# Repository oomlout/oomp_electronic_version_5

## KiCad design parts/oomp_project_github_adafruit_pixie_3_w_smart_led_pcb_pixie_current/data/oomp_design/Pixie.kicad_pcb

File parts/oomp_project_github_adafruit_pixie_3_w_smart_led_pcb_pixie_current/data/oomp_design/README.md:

# OOMP KiCad design copy

Open `Pixie.kicad_pro` (or the `.kicad_pcb` / `.kicad_sch`) in KiCad. Local OOMP libraries are under `libraries/`. Original inputs are preserved in [../original/](../original/).

Only verified unchanged installed KiCad defaults were renamed. Modified, custom, unmatched and unavailable items remain unchanged. Soldering variants are never swapped during conversion. Existing pad coordinates, nets and UUIDs are preserved.

See [conversion_report.yaml](conversion_report.yaml) for every conversion and skip. Copy this directory before editing; regeneration refuses to overwrite edited design files.

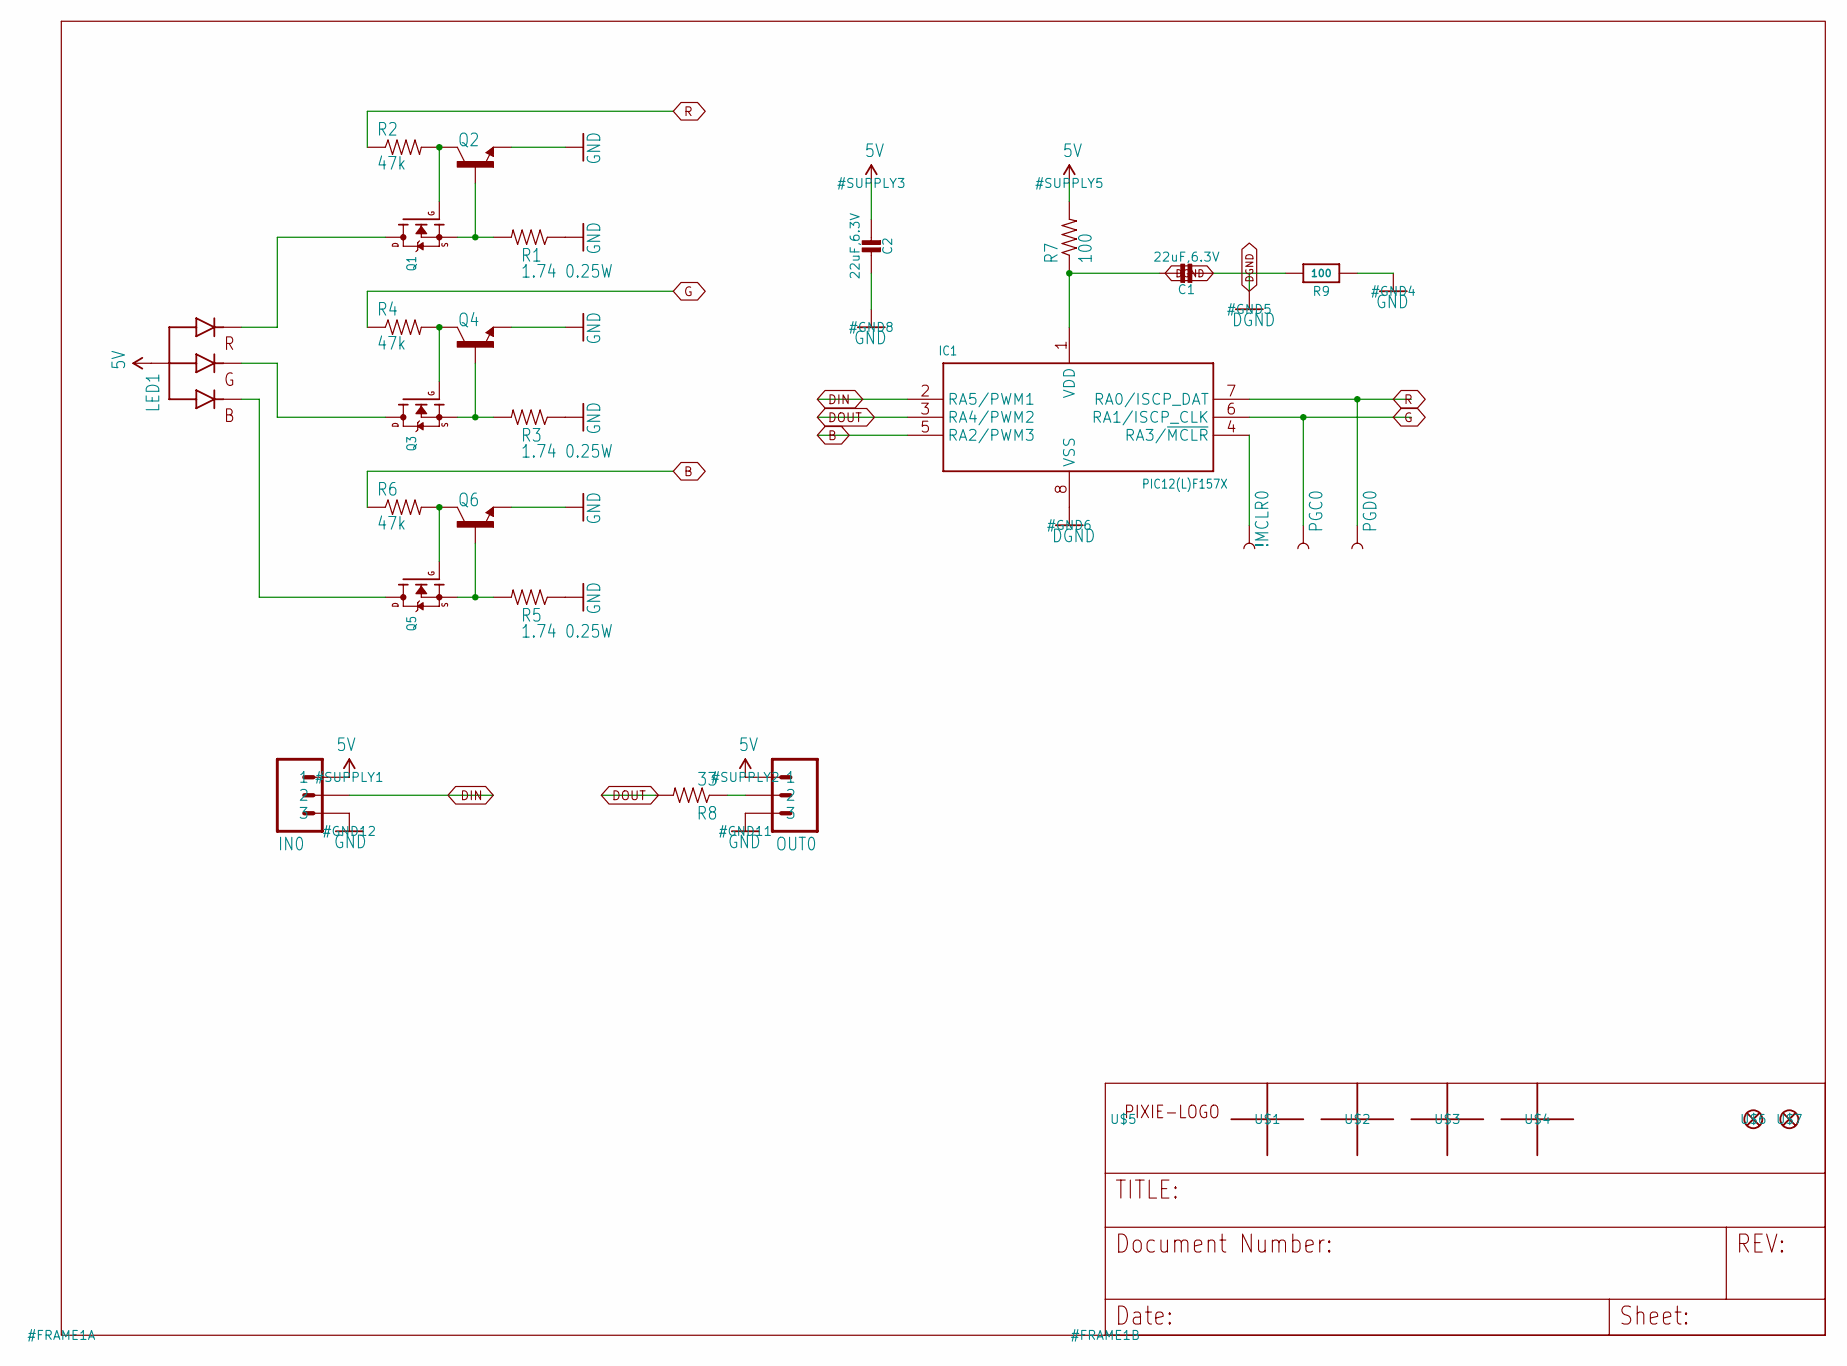
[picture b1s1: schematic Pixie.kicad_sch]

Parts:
!MCLR0: TEST-POINT3X4; PAD.03X.04
C1, C2: 22uF,6.3V; _0805MP
IC1: PIC12(L)F157X; MSOP-8
IN0: M030.1PWR+SIG; 1X03-0.1PWR+SIG
LED1: RGBLED_CA; RGBLED3W4PIN
OUT0: M030.1PWR+SIG; 1X03-0.1PWR+SIG
PGC0: TEST-POINT3X4; PAD.03X.04
PGD0: TEST-POINT3X4; PAD.03X.04
Q1, Q3, Q5: IRLML2060TRPBF; SOT23-3
Q2, Q4, Q6: MMBT2222A; SOT23-3
R1, R3, R5: 1.74 0.25W; 1206
R2, R4, R6: 47k; 0603-RES
R7: 100; 0603-RES
R8: 33; 0603-RES
R9: 100; _0603MP
U$1, U$2, U$3, U$4: ALIGN_CROSS
U$5: PIXIE-LOGO
U$6, U$7: FIDUCIAL""; FIDUCIAL_1MM

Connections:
5V: C2.2, IN0.P$1 (1), LED1.ANODE (VCC), OUT0.P$1 (1), R7.2
B: IC1.5 (RA2/PWM3), R6.1
DGND: C1.2, IC1.8 (VSS), R9.2
DIN: IC1.2 (RA5/PWM1), IN0.P$2 (2)
DOUT: IC1.3 (RA4/PWM2), R8.2
G: IC1.6 (RA1/ISCP_CLK), PGC0.P$1, R4.1
GND: C2.1, IN0.P$3 (3), OUT0.P$3 (3), Q2.2 (E), Q4.2 (E), Q6.2 (E), R1.1, R3.1, R5.1, R9.1
unnamed: LED1.R (RED), Q1.3 (D)
unnamed: LED1.G (GREEN), Q3.3 (D)
unnamed: LED1.B (BLUE), Q5.3 (D)
unnamed: Q1.2 (S), Q2.1 (B), R1.2
unnamed: Q3.2 (S), Q4.1 (B), R3.2
unnamed: OUT0.P$2 (2), R8.1
unnamed: !MCLR0.P$1, IC1.4 (RA3/~MCLR)
unnamed: Q5.1 (G), Q6.3 (C), R6.2
unnamed: Q3.1 (G), Q4.3 (C), R4.2
unnamed: C1.1, IC1.1 (VDD), R7.1
unnamed: Q5.2 (S), Q6.1 (B), R5.2
unnamed: Q1.1 (G), Q2.3 (C), R2.2
R: IC1.7 (RA0/ISCP_DAT), PGD0.P$1, R2.1

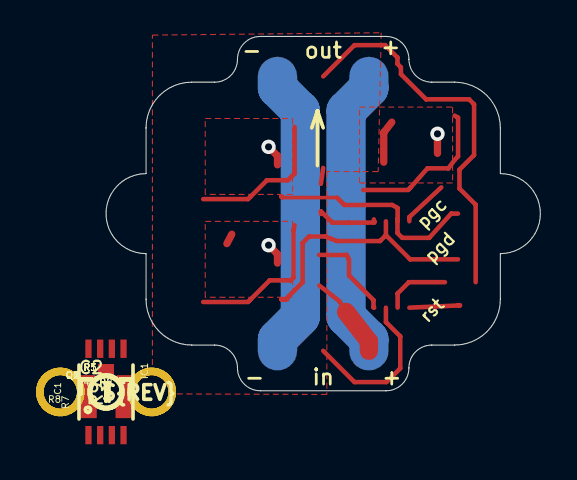
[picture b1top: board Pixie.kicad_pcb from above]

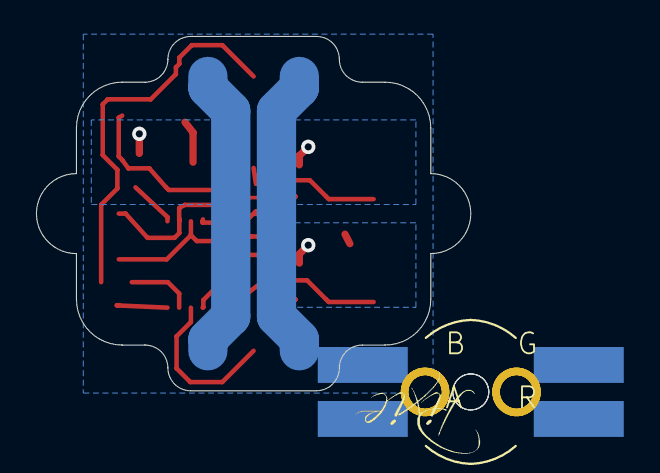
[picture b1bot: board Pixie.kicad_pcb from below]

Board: 16 copper layers, 24.1 x 19.7 mm, 34 parts (2 on the bottom side), 20 nets.

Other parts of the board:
U$8: PCBFEAT-REV-040
UNK_HOLE_0: dummyfp0
UNK_HOLE_1: dummyfp1

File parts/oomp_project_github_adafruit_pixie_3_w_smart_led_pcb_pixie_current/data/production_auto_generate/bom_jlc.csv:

Comment,Designator,Footprint,LCSC Part #
,U$8,Pixie-import-fps:PCBFEAT-REV-040,
1.74 0.25W,"R1,R3,R5",Pixie-import-fps:1206,
100,R7,Pixie-import-fps:0603-RES,C22775
100,R9,Pixie-import-fps:_0603MP,C22775
"22uF,6.3V","C1,C2",Pixie-import-fps:_0805MP,
33,R8,Pixie-import-fps:0603-RES,C23140
47k,"R2,R4,R6",Pixie-import-fps:0603-RES,C2907042
ALIGN_CROSS,"U$1,U$2,U$3,U$4",Pixie-import-fps:ALIGN_CROSS,
"FIDUCIAL""""","U$6,U$7",Pixie-import-fps:FIDUCIAL_1MM,
IRLML2060TRPBF,"Q1,Q3,Q5",Pixie-import-fps:SOT23-3,
MMBT2222A,"Q2,Q4,Q6",Pixie-import-fps:SOT23-3,
PIC12(L)F157X,IC1,Pixie-import-fps:MSOP-8,
PIXIE-LOGO,U$5,Pixie-import-fps:PIXIE-LOGO,
RGBLED_CA,LED1,Pixie-import-fps:RGBLED3W4PIN,
TEST-POINT3X4,"!MCLR0,PGC0,PGD0",Pixie-import-fps:PAD.03X.04,

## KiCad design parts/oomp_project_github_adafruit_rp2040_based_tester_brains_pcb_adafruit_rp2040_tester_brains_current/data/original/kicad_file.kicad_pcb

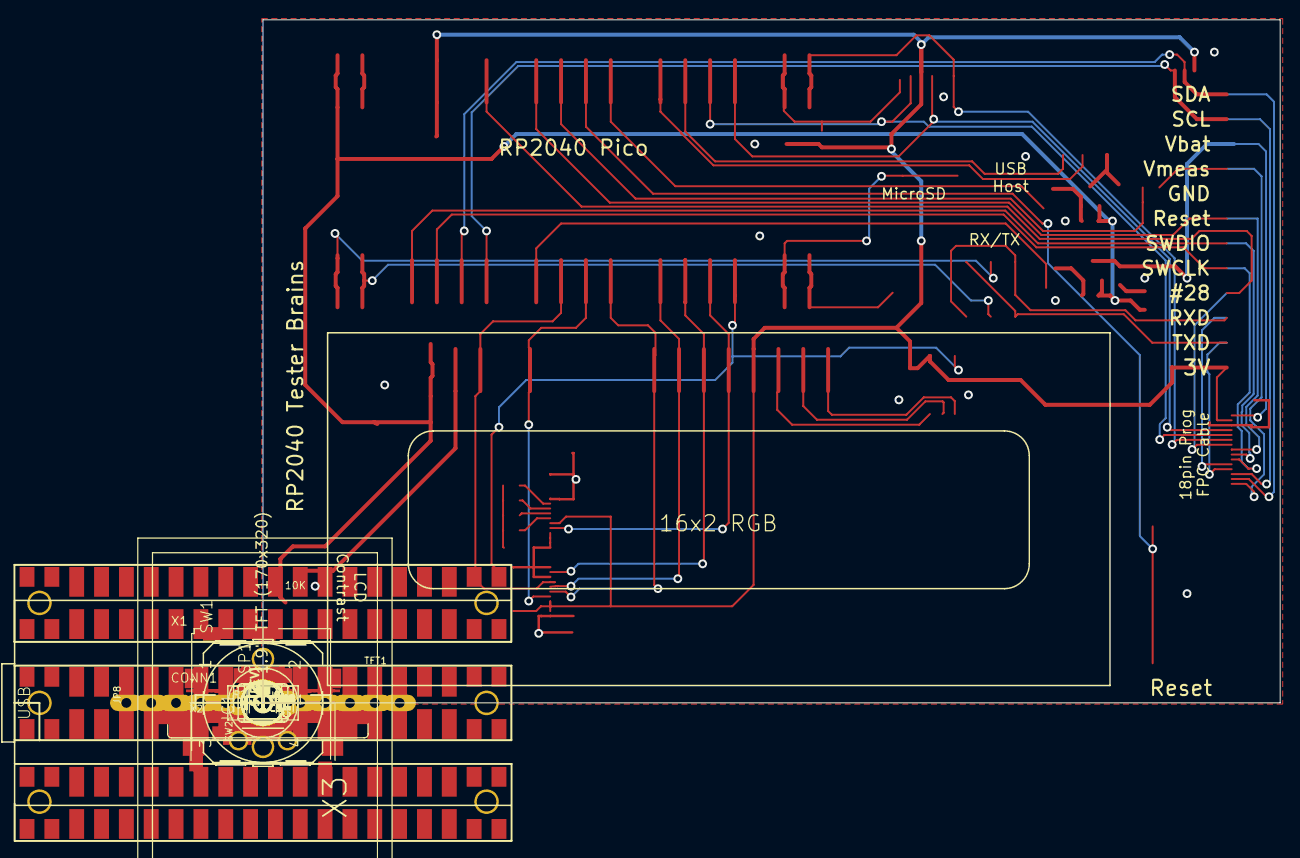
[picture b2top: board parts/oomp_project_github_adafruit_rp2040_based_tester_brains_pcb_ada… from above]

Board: 2 copper layers, 104.0 x 69.8 mm, 48 parts (0 on the bottom side), 47 nets.

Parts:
C1, C2, C3, C4, C5, C6, C7, C8, C9: 10uF; 0805-NO
CB1: PICOWBELL_DUALSMT
CONN1: STEMMA_I2C_QT; JST_SH4
FID1, FID2, FID3: FIDUCIAL_1MM
IC1: WS2811-SOP8; SO08-SKINNYPADS
JP1: 16x2 LCD; 2X20_SMT_MALE
JP8: 1X12_OVAL
Q1, Q2: DMG34x5; SOT23-WIDE
Q3, Q4, Q5: BSS138; SOT23-WIDE
R1, R2, R3, R4, R5: 10K; 0603-NO
R6, R7, R8, R9: 27; 0603-NO
SP1: SPEAKER/PS12; PS12
SW1: 12mm SMT; B3F-40XX-SMT
SW2: DPDT SLIDE; EG1390
TFT1: DISP_LCD_ST7789_1.9IN_SS; TFT_1.9IN_170X320_30P_SS
TP1, TP2, TP3, TP4: SEWTAP_SMTNUTM3; SMT_NUT_3MM
U$7, U$8, U$9, U$10: MOUNTINGHOLE3.0THIN; MOUNTINGHOLE_3.0_PLATEDTHIN
U$13: PCBFEAT-REV-040
VR1: 10K Trimmer; TRIMPOT_BOURNS_TC33X-2
X1: USB A; USB_HOST-SMT
X2: MicroSD; MICROSD
X3: TESTER_PROGCABLE_FLIP; FPC_0.5MM_18PIN

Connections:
3.3V: C2.1, C3.1, C5.1, C6.1, C7.1, CB1.S71, CB1.S72, CONN1.2, IC1.8, JP1.29, JP1.30, JP8.12, R5.1, TFT1.2, TFT1.3, TFT1.4, TFT1.20, X2.4, X3.2
+5V: C8.1, C9.1, CB1.S79, CB1.S80, JP1.3, JP1.4, Q1.2, Q2.2, R3.2, R4.2, VR1.1
GND: C1.2, C2.2, C3.2, C4.2, C5.2, C6.2, C7.2, C8.2, C9.2, CB1.S5, CB1.S6, CB1.S15, CB1.S16, CB1.S25, CB1.S26, CB1.S35, CB1.S36, CB1.S45, CB1.S46, CB1.S55, CB1.S56, CB1.S65, CB1.S66, CB1.S75, CB1.S76, CONN1.1, CONN1.MT1, CONN1.MT2, IC1.4, JP1.1, JP1.2, JP1.9, JP1.10, JP8.5, Q3.2, Q4.2, Q5.2, R2.1, SP1.P$1, SW1.P$3, SW1.P$4, TFT1.1, TFT1.9, TFT1.11, TFT1.12, TFT1.13, TFT1.14, TFT1.15, TFT1.16, TFT1.17, TFT1.18, TFT1.25, TFT1.30, TFT1.MNT1, TFT1.MNT2, TP1.P$1, TP2.P$1, TP3.P$1, TP4.P$1, VR1.3, X1.GND, X2.6, X2.MT1, X2.MT2, X3.3, X3.SUPPORT1, X3.SUPPORT2
GPIO28: CB1.S67, CB1.S68, JP8.9, X3.7
LCD_BLUE: IC1.3, JP1.35, JP1.36
LCD_D4: CB1.S23, CB1.S24, JP1.21, JP1.22, TFT1.6
LCD_D5: CB1.S27, CB1.S28, JP1.23, JP1.24, TFT1.7
LCD_D6: CB1.S29, CB1.S30, JP1.25, JP1.26, TFT1.10
LCD_D7: CB1.S31, CB1.S32, JP1.27, JP1.28, TFT1.19
LCD_E: CB1.S21, CB1.S22, JP1.11, JP1.12, TFT1.5
LCD_GREEN: IC1.2, JP1.33, JP1.34
LCD_NEO: CB1.S33, CB1.S34, IC1.6, Q5.1
LCD_RED: IC1.1, JP1.31, JP1.32
LCD_RS: CB1.S19, CB1.S20, JP1.7, JP1.8, TFT1.8
LEDK: Q5.3, R6.1, R7.1, R8.1, R9.1
MISO: CB1.S41, CB1.S42, X2.7, X3.6
MOSI: CB1.S49, CB1.S50, X2.3, X3.5
unnamed: CB1.S39, CB1.S40, SP1.P$2
unnamed: R6.2, TFT1.21
unnamed: R7.2, TFT1.22
unnamed: R8.2, TFT1.23
unnamed: R9.2, TFT1.24
unnamed: JP1.5, JP1.6, VR1.2
RESET: CB1.S59, CB1.S60, SW1.P$1, SW1.P$2
RXD: CB1.S3, CB1.S4, SW2.P1
RXI: JP8.10, SW2.O2, SW2.S1, X3.11
SCK: CB1.S47, CB1.S48, X2.5, X3.4
SCL: CB1.S13, CB1.S14, CONN1.4, JP8.2, X3.13
SDA: CB1.S11, CB1.S12, CONN1.3, JP8.1, X3.14
SD_CD: CB1.S37, CB1.S38, X2.CD1, X2.CD2
SD_CS: CB1.S43, CB1.S44, R5.2, X2.2
SWCLK: CB1.S9, CB1.S10, JP8.8, X3.10
SWDIO: CB1.S7, CB1.S8, JP8.7, X3.9
TARGET_RESET: CB1.S63, CB1.S64, JP8.6, X3.8
TXD: CB1.S1, CB1.S2, SW2.P2
TXO: JP8.11, SW2.O1, SW2.S2, X3.12
USB_D+: CB1.S51, CB1.S52, X1.D+
USB_D-: CB1.S53, CB1.S54, X1.D-
VBAT: C1.1, JP8.3, Q2.3, X3.1
VBAT_SW: CB1.S17, CB1.S18, Q4.1
VMEAS: JP8.4, R1.2, X3.15
VMEAS_DIV2: CB1.S61, CB1.S62, R1.1, R2.2
VSYS: CB1.S77, CB1.S78
VUSB: C4.1, Q1.3, X1.VBUS
VUSB_SW: CB1.S57, CB1.S58, Q3.1
~VBAT_SW1: Q2.1, Q4.3, R4.1
~VBAT_SW2: Q1.1, Q3.3, R3.1

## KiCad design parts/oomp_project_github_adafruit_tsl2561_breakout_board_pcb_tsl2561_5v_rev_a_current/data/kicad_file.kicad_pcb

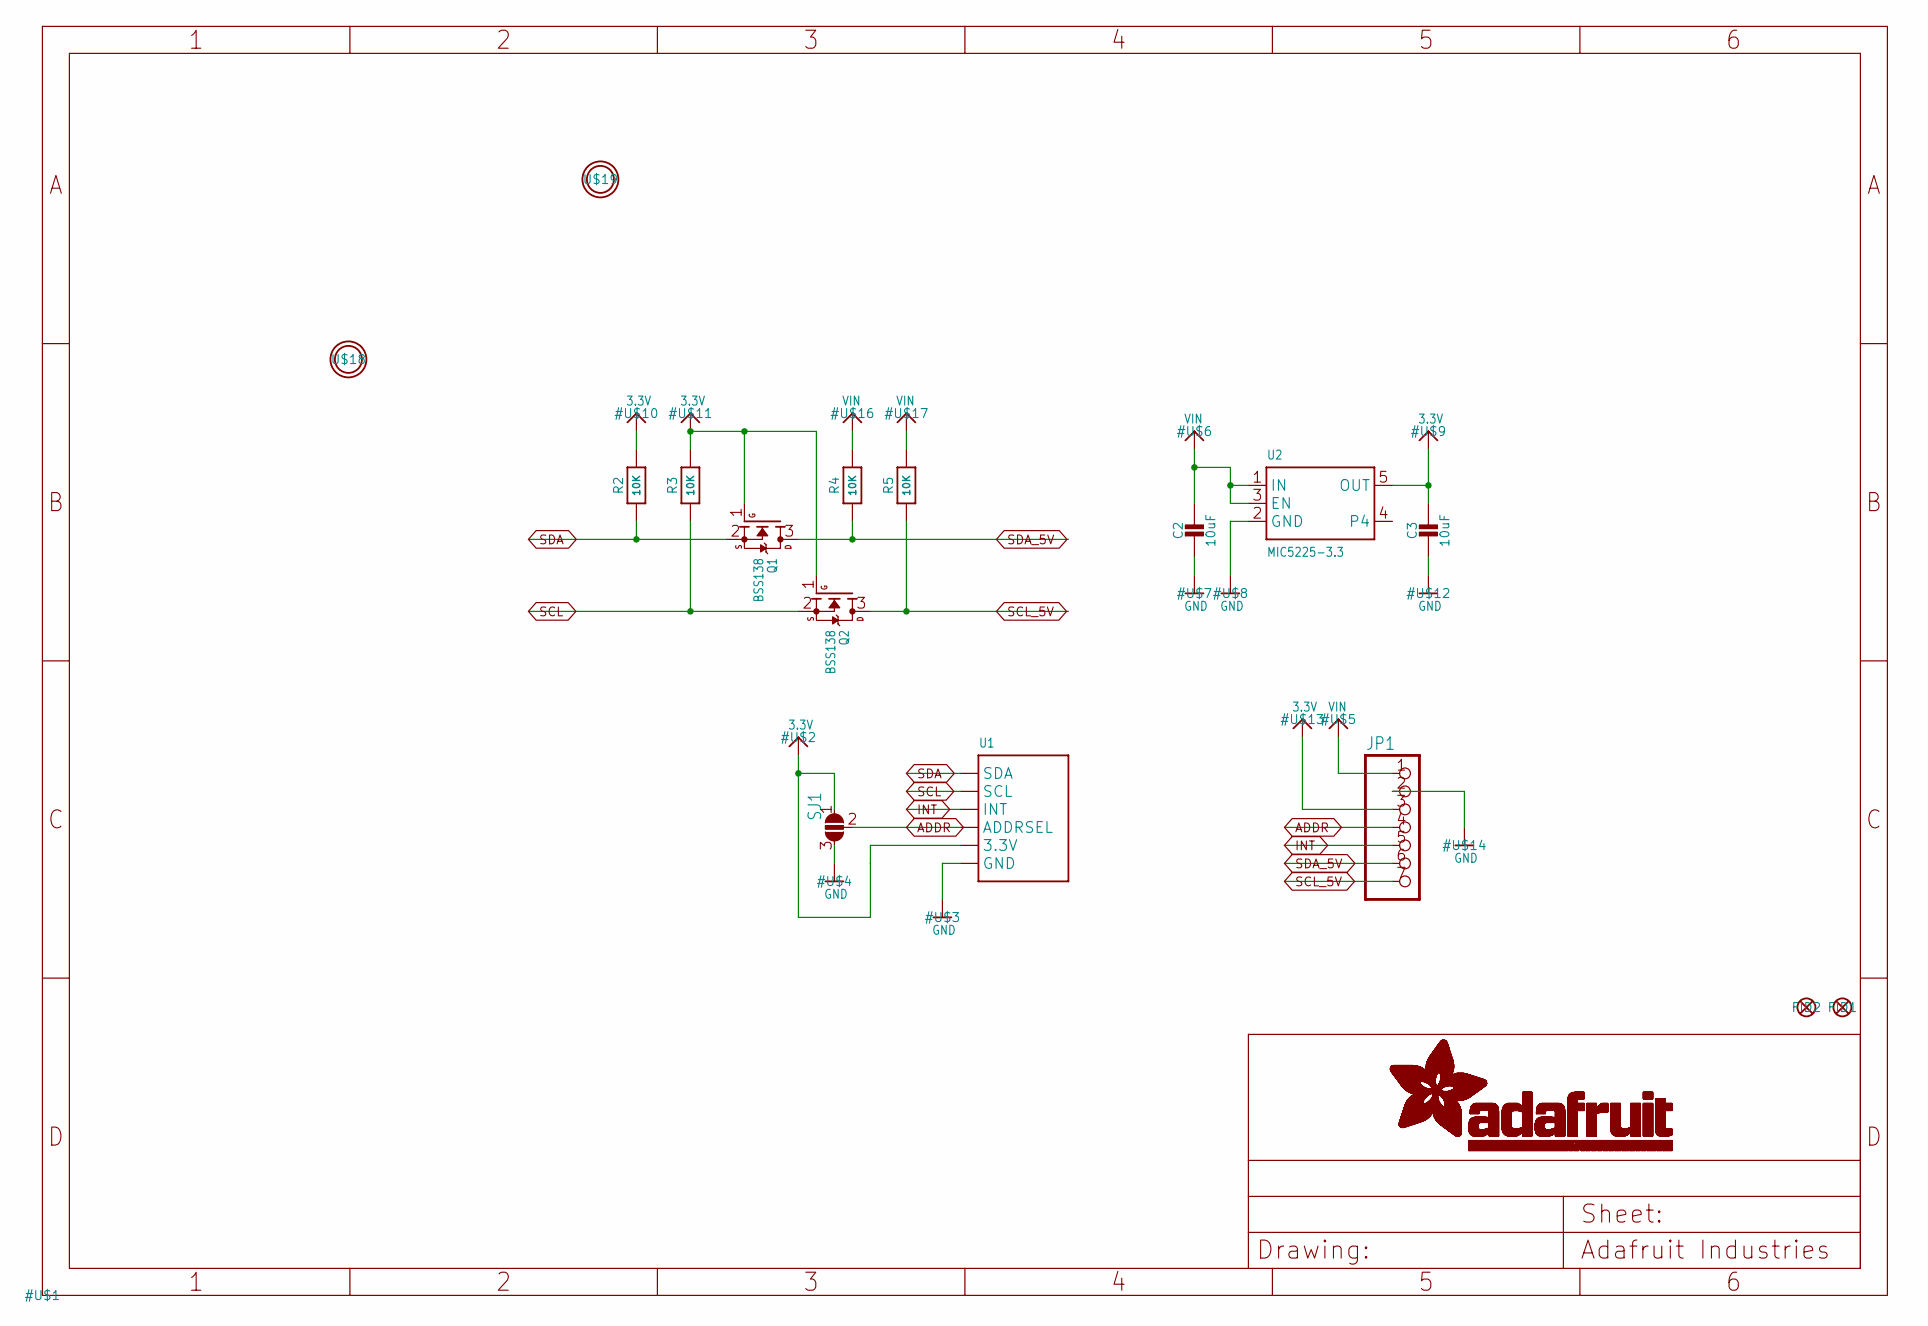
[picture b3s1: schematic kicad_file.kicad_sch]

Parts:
C2, C3: 10uF; 0805-NO
FID1, FID2: FIDUCIAL""; FIDUCIAL_1MM
JP1: HEADER-1X7THICKER; 1X07_ROUND_76
Q1, Q2: BSS138; SOT23-WIDE
R2, R3, R4, R5: 10K; 0805-NO
SJ1: SOLDERJUMPER_2WAY; SOLDERJUMPER_2WAY_OPEN_NOPASTE
U1: LIGHT_TSL2561; TSL2561_FN
U2: MIC5225-3.3; SOT23-5
U$18, U$19: MOUNTINGHOLE2.5; MOUNTINGHOLE_2.5_PLATED

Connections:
3.3V: C3.1, JP1.3, Q1.1 (G), Q2.1 (G), R2.2, R3.2, SJ1.1, U1.VDD (3.3V), U2.5 (OUT)
ADDR: JP1.4, SJ1.2, U1.ADR (ADDRSEL)
GND: C2.2, C3.2, JP1.2, SJ1.3, U1.VSS (GND), U2.2 (GND)
INT: JP1.5, U1.INT
SCL: Q2.2 (S), R3.1, U1.CLK (SCL)
SCL_5V: JP1.7, Q2.3 (D), R5.1
SDA: Q1.2 (S), R2.1, U1.DATA (SDA)
SDA_5V: JP1.6, Q1.3 (D), R4.1
VIN: C2.1, JP1.1, R4.2, R5.2, U2.1 (IN), U2.3 (EN)

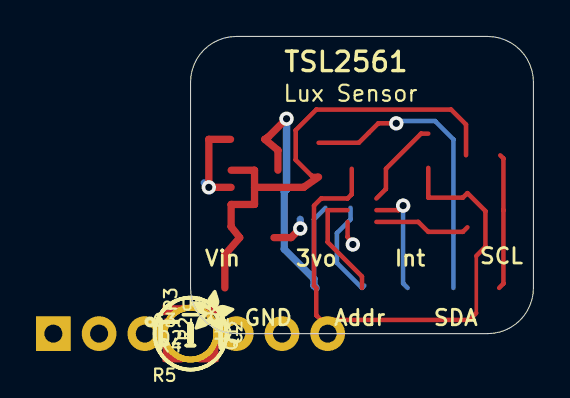
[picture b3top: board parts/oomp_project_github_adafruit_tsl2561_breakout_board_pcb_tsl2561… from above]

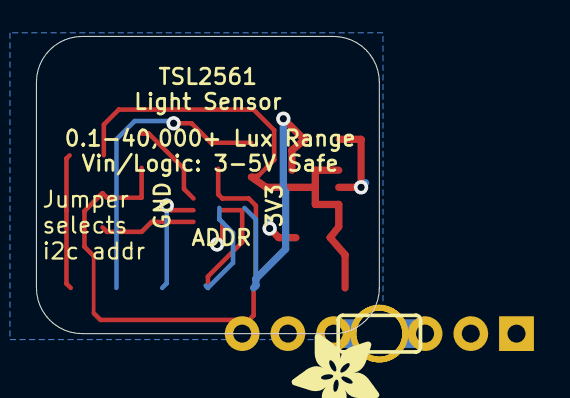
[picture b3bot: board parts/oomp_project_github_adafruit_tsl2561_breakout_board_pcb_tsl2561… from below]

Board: 2 copper layers, 19.1 x 16.5 mm, 18 parts (2 on the bottom side), 9 nets.

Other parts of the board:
U$15: ADAFRUIT_2.5MM
U$20: ADAFRUIT_5MM

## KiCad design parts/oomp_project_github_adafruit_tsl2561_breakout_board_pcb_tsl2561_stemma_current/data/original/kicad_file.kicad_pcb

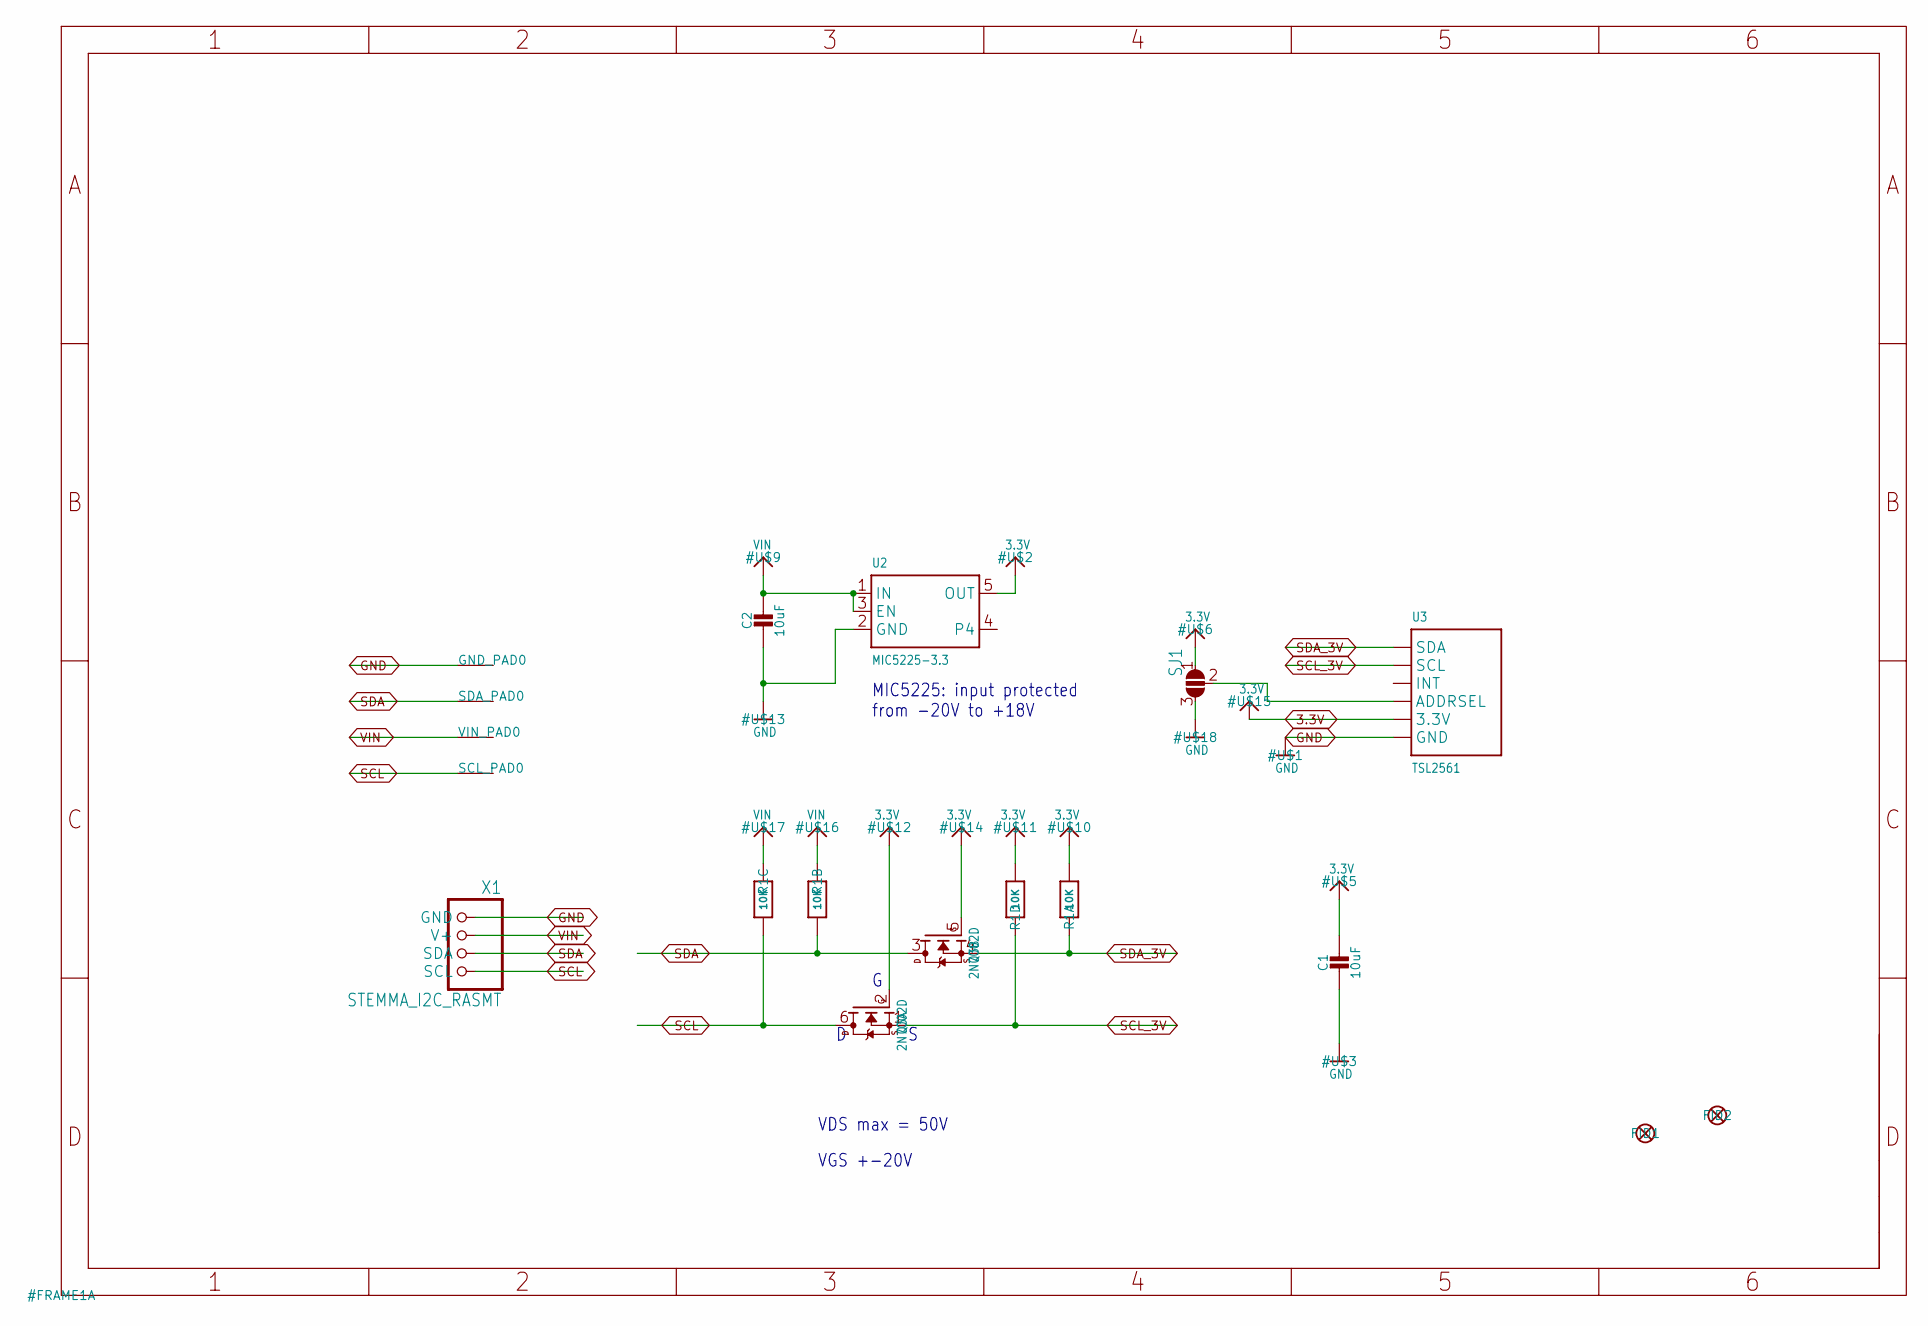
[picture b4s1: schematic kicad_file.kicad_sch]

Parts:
C1, C2: 10uF; 0805-NO
FID1, FID2: FIDUCIAL_1MM
GND_PAD0: SEWTAP-ALLIGATOR; SEWALLI
Q3: 2N7002D; SOT363
R1: 10K; RESPACK_4X0603
SCL_PAD0: SEWTAP-ALLIGATOR; SEWALLI
SDA_PAD0: SEWTAP-ALLIGATOR; SEWALLI
SJ1: SOLDERJUMPER_2WAY; SOLDERJUMPER_2WAY_OPEN_NOPASTE
U2: MIC5225-3.3; SOT23-5
U3: TSL2561; TSL2561_FN
VIN_PAD0: SEWTAP-ALLIGATOR; SEWALLI
X1: STEMMA_I2C_RASMT; JSTPH4

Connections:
3.3V: C1.1, Q3.2 (G), Q3.5 (G), R1.1, R1.5 (2), SJ1.1, U2.5 (OUT), U3.VDD (3.3V)
GND: C1.2, C2.2, GND_PAD0.P$1, SJ1.3, U2.2 (GND), U3.VSS (GND), X1.1 (GND)
unnamed: SJ1.2, U3.ADR (ADDRSEL)
SCL: Q3.6 (D), R1.6 (2), SCL_PAD0.P$1, X1.4 (SCL)
SCL_3V: Q3.1 (S), R1.4 (1), U3.CLK (SCL)
SDA: Q3.3 (D), R1.7 (2), SDA_PAD0.P$1, X1.3 (SDA)
SDA_3V: Q3.4 (S), R1.8 (2), U3.DATA (SDA)
VIN: C2.1, R1.2 (1), R1.3 (1), U2.1 (IN), U2.3 (EN), VIN_PAD0.P$1, X1.2 (V+)

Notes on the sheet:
VDS max = 50V
VGS +-20V
MIC5225: input protected from -20V to +18V

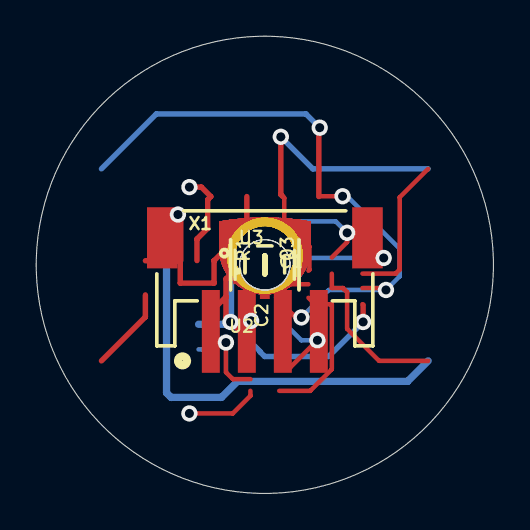
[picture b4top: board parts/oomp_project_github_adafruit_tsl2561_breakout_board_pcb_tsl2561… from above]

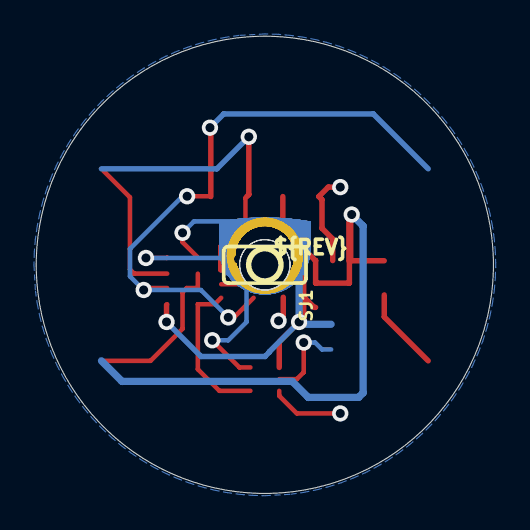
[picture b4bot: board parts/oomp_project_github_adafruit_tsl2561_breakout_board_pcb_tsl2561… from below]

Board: 2 copper layers, 25.4 x 25.4 mm, 19 parts (3 on the bottom side), 8 nets.

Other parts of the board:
U$4: STEMMA_TSL2561_B_FRONT
U$7: STEMMA_TSL2561_B_BACK
U$8: PCBFEAT-REV-040
UNK_HOLE_0: dummyfp0
UNK_HOLE_1: dummyfp1

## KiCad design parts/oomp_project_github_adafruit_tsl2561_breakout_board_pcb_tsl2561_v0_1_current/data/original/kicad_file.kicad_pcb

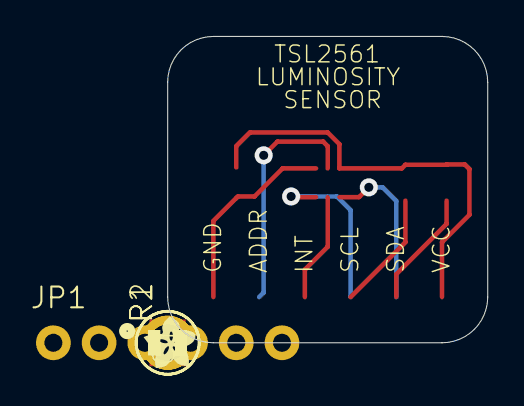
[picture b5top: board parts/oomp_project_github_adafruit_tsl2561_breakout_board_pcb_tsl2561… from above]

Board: 2 copper layers, 17.8 x 17.0 mm, 10 parts (0 on the bottom side), 6 nets.

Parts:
C1: 0.1uF; C0805
JP1: 1X06_ROUND_76
R1, R2: 10K; R0805
U1: TSL2561; TSL2561_FN
U$2, U$4: FIDUCIAL; FIDUCIAL_1MM
U$5, U$6: MOUNTINGHOLE2.0; MOUNTINGHOLE_2.0_PLATED
U$7: ADAFRUIT200MIL

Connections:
ADDR: JP1.2, U1.ADR
GND: C1.2, JP1.1, U1.VSS
INT: JP1.3, U1.INT
SCL: JP1.4, R2.1, U1.CLK
SDA: JP1.5, R1.1, U1.DATA
VCC: C1.1, JP1.6, R1.2, R2.2, U1.VDD

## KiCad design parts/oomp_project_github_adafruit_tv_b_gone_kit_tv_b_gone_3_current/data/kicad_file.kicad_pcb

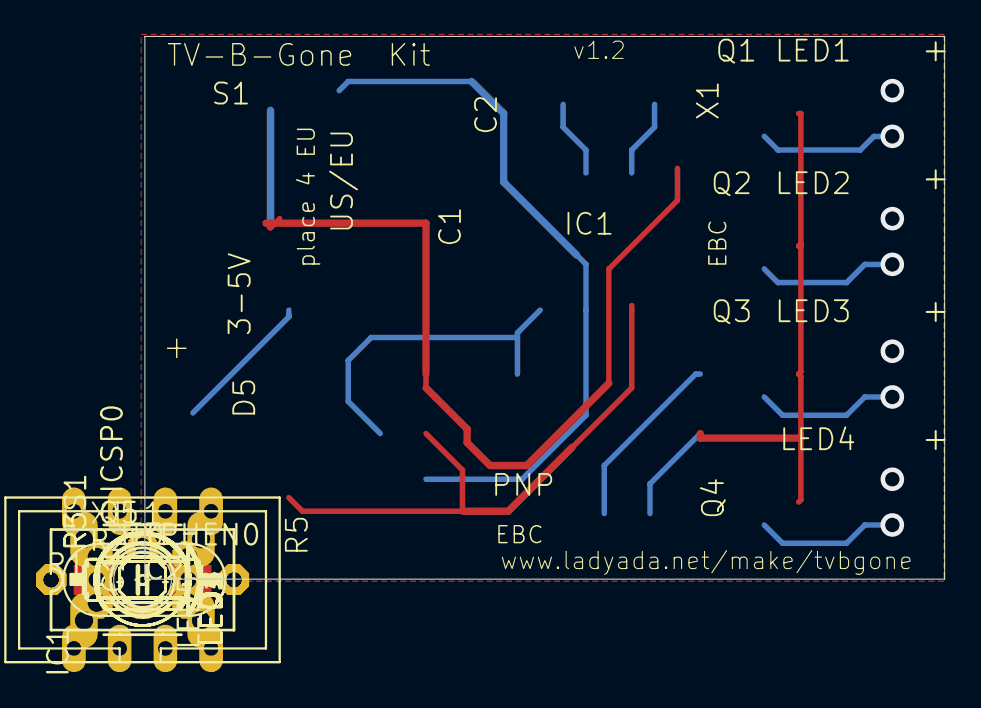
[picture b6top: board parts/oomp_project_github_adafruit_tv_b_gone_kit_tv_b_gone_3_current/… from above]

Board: 16 copper layers, 44.4 x 30.1 mm, 23 parts (0 on the bottom side), 15 nets.

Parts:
+0: 1X01
C1: 0.1uF; C025-025X050
C2: 100uF; E2,5-5
HYPHEN0: 1X01
IC1: ATTINY85V-10P; DIL08
ICSP0: PINHD-2X3THM; ISP6
LED1, LED2, LED3, LED4: LED; 5MM-SIDE
LED5: RED; LED3MM
Q1, Q2, Q3, Q4: 2N3904; TO92-EZ
Q5: MPS2907A; TO92-CBE
R1: 1.0 K; 0207_10
R2: 10K (opt); 0207_10
R3: 10K; 0207_10
R5: 1K; 0207_10
S1: B3F-10XX
UNK_HOLE_0: dummyfp0
XTL1: 8.0MHz; CERM_OSC

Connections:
GND: C1.2, C2.-, HYPHEN0.1, IC1.4, ICSP0.6, Q1.3, Q2.3, Q3.3, Q4.3, R2.1, R3.1, S1.1, S1.2, XTL1.P$2
MISO: IC1.6, ICSP0.1, R3.2
MOSI: IC1.5, ICSP0.4, R1.2
unnamed: IC1.3, XTL1.P$1
unnamed: IC1.2, XTL1.P$3
unnamed: LED5.K, R5.2
unnamed: Q5.B, R1.1
unnamed: LED4.K, LED4.K2, Q4.1
unnamed: LED2.K, LED2.K2, Q2.1
unnamed: LED3.K, LED3.K2, Q3.1
unnamed: Q1.2, Q2.2, Q3.2, Q4.2, Q5.C, R2.2
unnamed: LED1.K, LED1.K2, Q1.1
RST: IC1.1, ICSP0.5, S1.3, S1.4
SCK: IC1.7, ICSP0.3, R5.1
VCC: +0.1, C1.1, C2.+, IC1.8, ICSP0.2, LED1.A, LED1.A2, LED2.A, LED2.A2, LED3.A, LED3.A2, LED4.A, LED4.A2, LED5.A, Q5.E

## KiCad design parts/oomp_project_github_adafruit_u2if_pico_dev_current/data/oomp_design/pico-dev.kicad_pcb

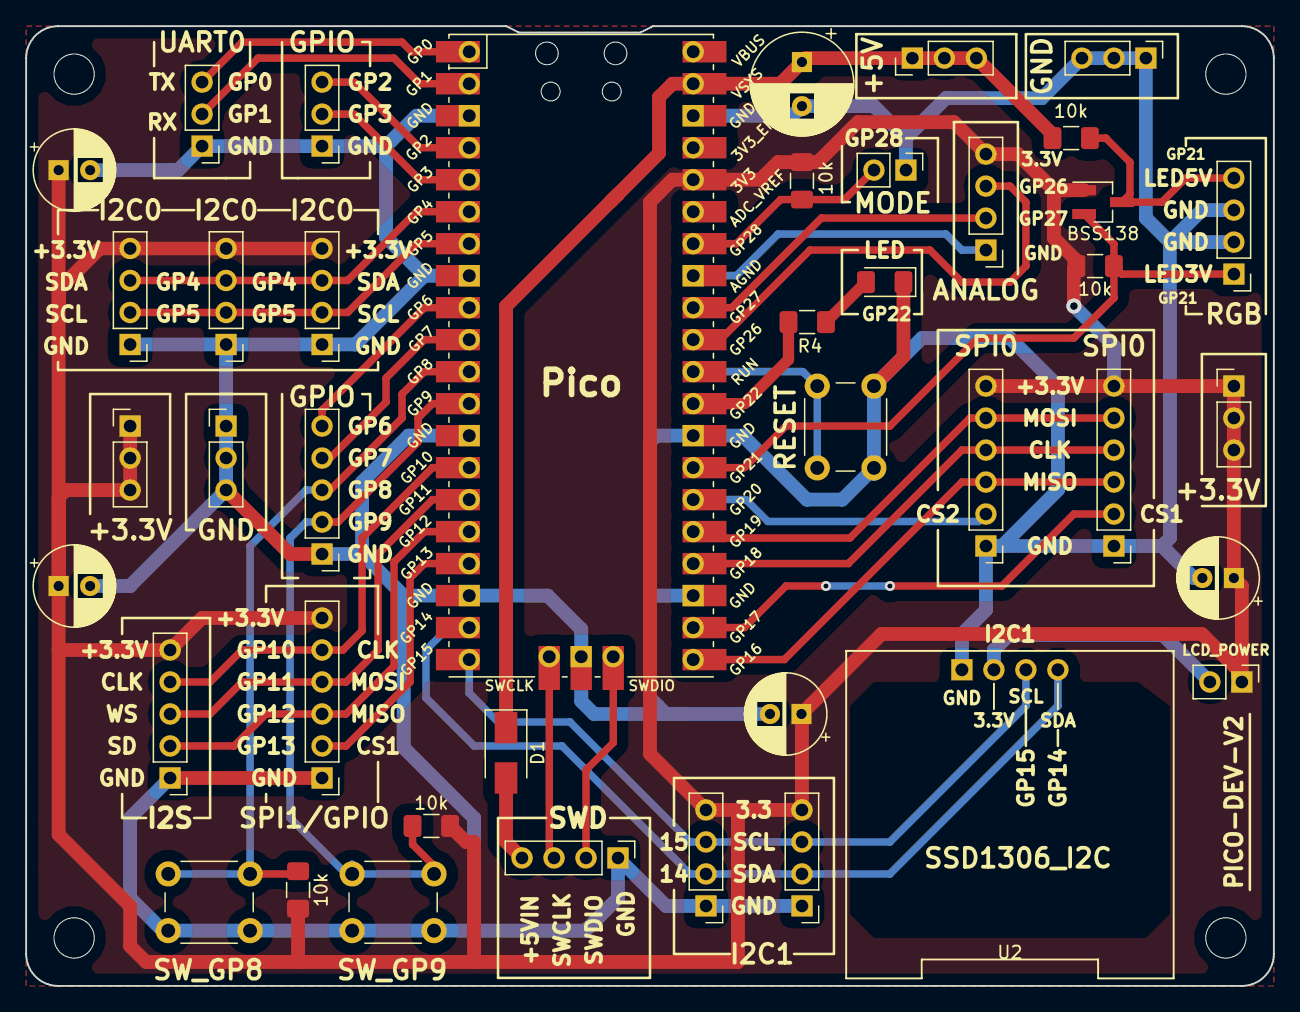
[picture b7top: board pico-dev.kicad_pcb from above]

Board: 2 copper layers, 99.1 x 76.2 mm, 45 parts (0 on the bottom side), 37 nets.

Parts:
C1: CP; CP_Radial_D8.0mm_P3.50mm
C2, C3, C4, C5: CP; CP_Radial_D6.3mm_P2.50mm
D1: SS14; D_SMA
D2: LED; LED_1206_3216Metric_Pad1.42x1.75mm_HandSolder
H1, H2, H3, H4: MountingHole; MountingHole_3.2mm_M3
J1: MODE; PinHeader_1x02_P2.54mm_Vertical
J2: SWD; PinHeader_1x04_P2.54mm_Vertical
J3: ANALOG; PinHeader_1x04_P2.54mm_Vertical
J5, J6, J7: I2C0; PinHeader_1x04_P2.54mm_Vertical
J8: UART0; PinHeader_1x03_P2.54mm_Vertical
J9, J10: SPI0; PinHeader_1x06_P2.54mm_Vertical
J12: SPI1/GPIO; PinHeader_1x06_P2.54mm_Vertical
J13, J17: +3.3V; PinHeader_1x03_P2.54mm_Vertical
J14: +5V; PinHeader_1x03_P2.54mm_Vertical
J15, J16: GND; PinHeader_1x03_P2.54mm_Vertical
J18: GPIO; PinHeader_1x05_P2.54mm_Vertical
J19: I2S; PinHeader_1x05_P2.54mm_Vertical
J20: GPIO; PinHeader_1x03_P2.54mm_Vertical
J21: RGB; PinHeader_1x04_P2.54mm_Vertical
J22, J23: I2C1; PinHeader_1x04_P2.54mm_Vertical
JP1: LCD_POWER; PinHeader_1x02_P2.54mm_Vertical
Q1: BSS138; SOT-23_Handsoldering
R1, R2, R3, R5, R6: 10k; R_1206_3216Metric_Pad1.42x1.75mm_HandSolder
R4: 470; R_1206_3216Metric_Pad1.42x1.75mm_HandSolder
SW1: RESET; SW_PUSH_6mm_H4.3mm
SW2: SW_GP9; SW_PUSH_6mm_H4.3mm
SW3: SW_GP8; SW_PUSH_6mm_H4.3mm
U1: Pico; RPi_Pico_SMD_TH
U2: SSD1306_I2C; ssd1306_I2c

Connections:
+3V3: C2.1, C3.1, C4.1, C5.1, J3.4, J5.4, J6.4, J7.4, J9.6, J10.6, J12.6, J13.1, J13.2, J13.3, J17.1, J17.2, J17.3, J19.5, J22.4, J23.4, JP1.1, Q1.1, R1.1, R2.1, R3.1, R5.1, U1.36
+5V: C1.1, D1.1, J14.1, J14.2, J14.3, R6.1, U1.39
+5VD: D1.2, J2.4
ADC0: J3.3, U1.31
ADC1: J3.2, U1.32
AGND: J3.1, U1.33
GND: C1.2, C2.2, C3.2, C4.2, C5.2, D2.1, J1.1, J2.1, J5.1, J6.1, J7.1, J8.1, J9.1, J10.1, J12.1, J15.1, J15.2, J15.3, J16.1, J16.2, J16.3, J18.1, J19.1, J20.1, J21.2, J21.3, J22.1, J23.1, SW1.2, SW2.2, SW3.2, U1.3, U1.8, U1.13, U1.18, U1.23, U1.28, U1.38, U1.42, U2.1
GP2: J20.3, U1.4
GP3: J20.2, U1.5
GP6: J18.5, U1.9
GP7: J18.4, U1.10
GP8: J18.3, R3.2, SW3.1, U1.11
GP9: J18.2, R2.2, SW2.1, U1.12
LED: R4.2, U1.29
MODE: J1.2, R1.2, U1.34
unnamed: D2.2, R4.1
unnamed: JP1.2, U2.2
RUN: SW1.1, U1.30
SCL1_GP15: J22.3, J23.3, U1.20, U2.3
SCL_0: J5.2, J6.2, J7.2, U1.7
SDA1_GP14: J22.2, J23.2, U1.19, U2.4
SDA_0: J5.3, J6.3, J7.3, U1.6
SPI0_CK: J9.4, J10.4, U1.24
SPI0_CS1: J9.2, U1.22
SPI0_CS2: J10.2, U1.26
SPI0_MISO: J9.3, J10.3, U1.21
SPI0_MOSI: J9.5, J10.5, U1.25
SPI1_CK_GP10_I2S_CLK: J12.5, J19.4, U1.14
SPI1_CS1_GP13: J12.2, U1.17
SPI1_MISO_GP12_I2S_SD: J12.3, J19.2, U1.16
SPI1_MOSI_GP11_I2S_WS: J12.4, J19.3, U1.15
SWCLK: J2.3, U1.41
SWDIO: J2.2, U1.43
U_RX: J8.2, U1.2
U_TX: J8.3, U1.1
WS2812B_5V: J21.4, Q1.3, R6.2
WS2812_3V: J21.1, Q1.2, R5.2, U1.27
